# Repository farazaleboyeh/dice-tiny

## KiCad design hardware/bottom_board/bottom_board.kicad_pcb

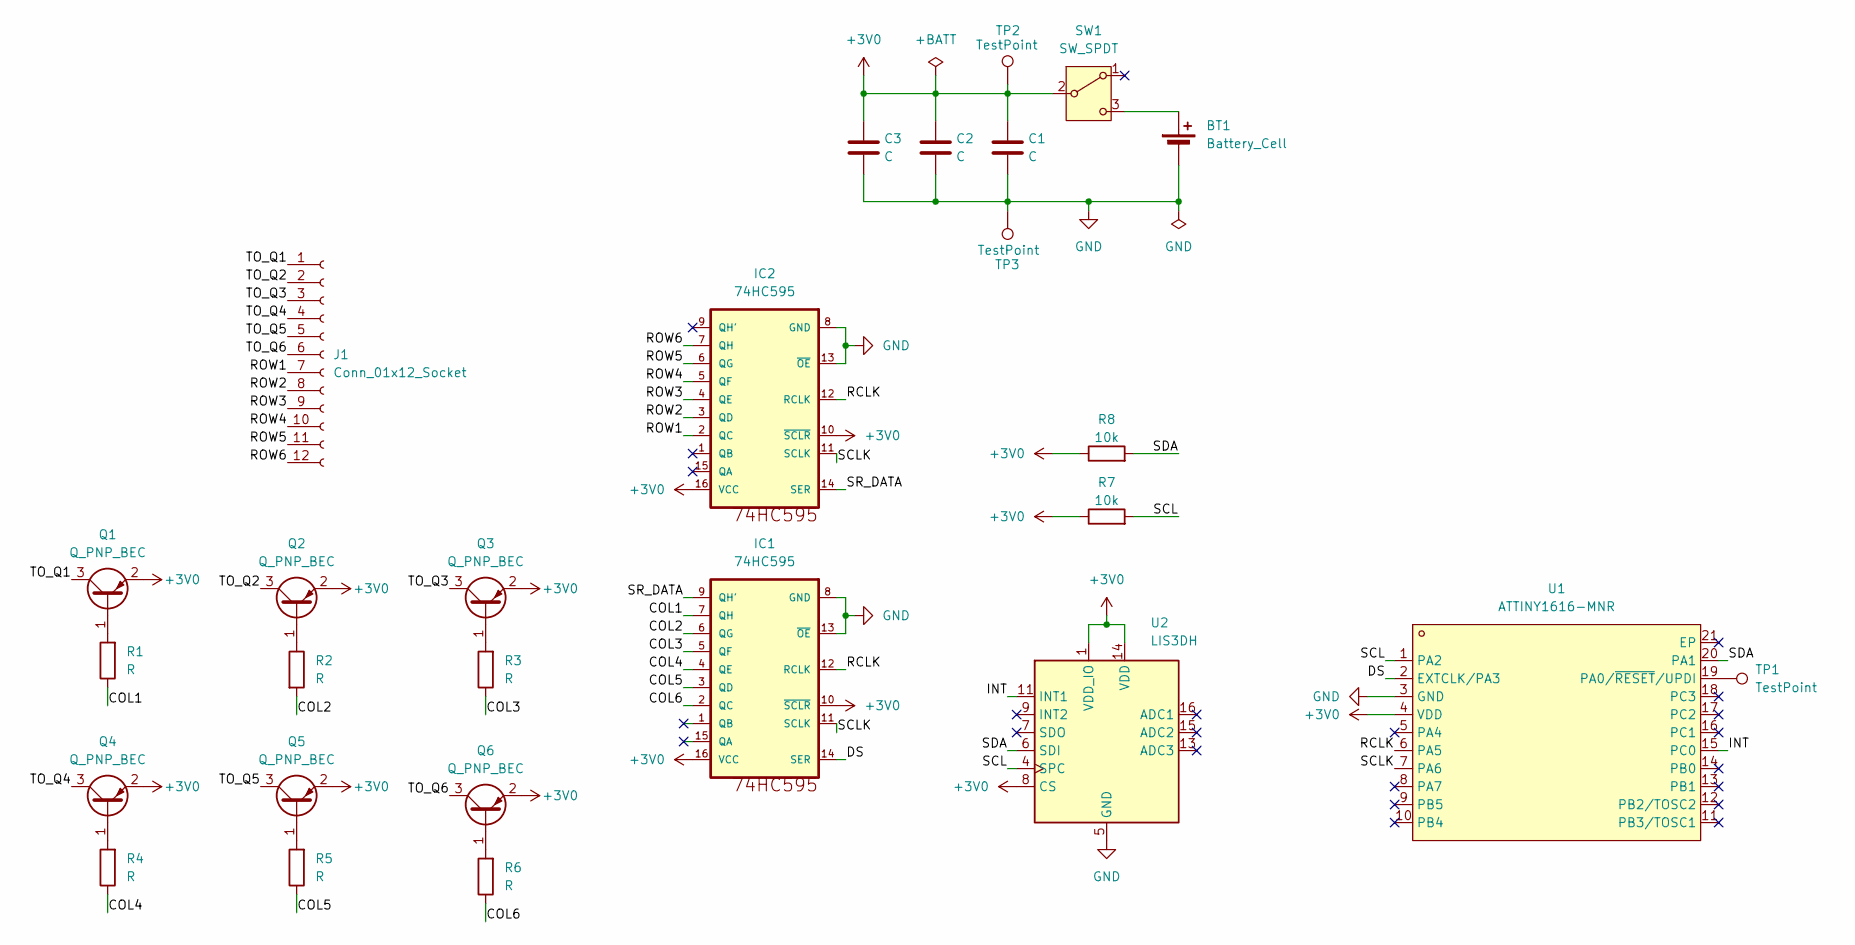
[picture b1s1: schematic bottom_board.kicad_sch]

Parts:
BT1: Battery_Cell; BAT-SMD_MY-2032-12-Updated-4; LCSC Part C6937139
C1, C3: C; C_0402_1005Metric
C2: C; C_0805_2012Metric
IC1, IC2: 74HC595; DHVQFN-16-1EP_2.5x3.5mm_P0.5mm_EP1x2mm
J1: Conn_01x12_Socket; PinSocket_1x12_P1.27mm_Vertical
Q1, Q2, Q3, Q4, Q5, Q6: Q_PNP_BEC; SOT-523
R1, R2, R3, R4, R5, R6: R; R_0402_1005Metric
R7, R8: 10k; R_0402_1005Metric
SW1: SW_SPDT; SW-SMD_MSK12CO2; LCSC Part C2681570
TP1, TP2, TP3: TestPoint; TestPoint_Pad_D1.0mm
U1: ATTINY1616-MNR; QFN-20_L3.0-W3.0-P0.40-BL-EP1.7; MPN ATTINY1616-MNR; LCSC Part C507118
U2: LIS3DH; LGA-16_3x3mm_P0.5mm_LayoutBorder3x5y

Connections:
+3V0: C1.1, C2.1, C3.1, IC1.10 (~SCLR), IC1.16 (VCC), IC2.10 (~SCLR), IC2.16 (VCC), Q1.2 (E), Q2.2 (E), Q3.2 (E), Q4.2 (E), Q5.2 (E), Q6.2 (E), R7.1, R8.1, SW1.2 (B), TP2.1 (1_1), U1.4 (VDD), U2.1 (VDD_IO), U2.8 (CS), U2.14 (VDD)
/COL1: IC1.7 (QH), R1.1
/COL2: IC1.6 (QG), R2.2
/COL3: IC1.5 (QF), R3.1
/COL4: IC1.4 (QE), R4.1
/COL5: IC1.3 (QD), R5.1
/COL6: IC1.2 (QC), R6.1
/DS: IC1.14 (SER), U1.2 (EXTCLK/PA3)
/INT: U1.15 (PC0), U2.11 (INT1)
/RCLK: IC1.12 (RCLK), IC2.12 (RCLK), U1.6 (PA5)
/ROW1: IC2.2 (QC), J1.7
/ROW2: IC2.3 (QD), J1.8
/ROW3: IC2.4 (QE), J1.9
/ROW4: IC2.5 (QF), J1.10
/ROW5: IC2.6 (QG), J1.11
/ROW6: IC2.7 (QH), J1.12
/SCL: R7.2, U1.1 (PA2), U2.4 (SPC)
/SCLK: IC1.11 (SCLK), IC2.11 (SCLK), U1.7 (PA6)
/SDA: R8.2, U1.20 (PA1), U2.6 (SDI)
/SR_DATA: IC1.9 (QH'), IC2.14 (SER)
/TO_Q1: J1.1, Q1.3 (C)
/TO_Q2: J1.2, Q2.3 (C)
/TO_Q3: J1.3, Q3.3 (C)
/TO_Q4: J1.4, Q4.3 (C)
/TO_Q5: J1.5, Q5.3 (C)
/TO_Q6: J1.6, Q6.3 (C)
GND: BT1.2 (-), C1.2, C2.2, C3.2, IC1.8 (GND), IC1.13 (~OE), IC2.8 (GND), IC2.13 (~OE), TP3.1 (1_1), U1.3 (GND), U2.5 (GND), U2.10 (GND), U2.12 (GND)
unnamed: BT1.1 (+), SW1.3 (C)
unnamed: Q1.1 (B), R1.2
unnamed: Q2.1 (B), R2.1
unnamed: Q3.1 (B), R3.2
unnamed: Q4.1 (B), R4.2
unnamed: Q5.1 (B), R5.2
unnamed: Q6.1 (B), R6.2
unnamed: TP1.1 (1_1), U1.19 (PA0/~RESET/UPDI)

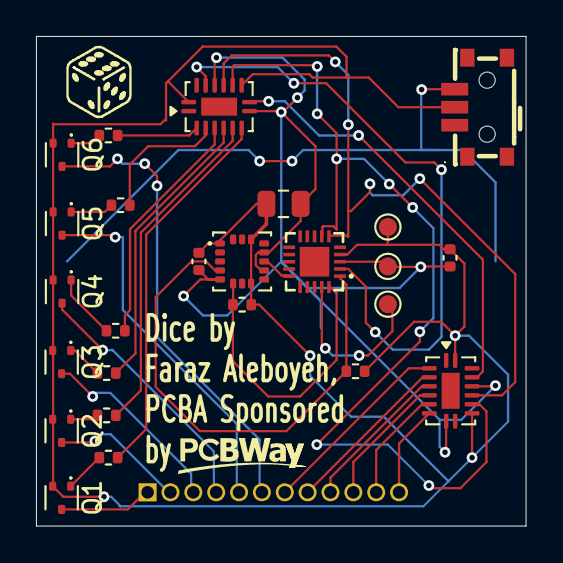
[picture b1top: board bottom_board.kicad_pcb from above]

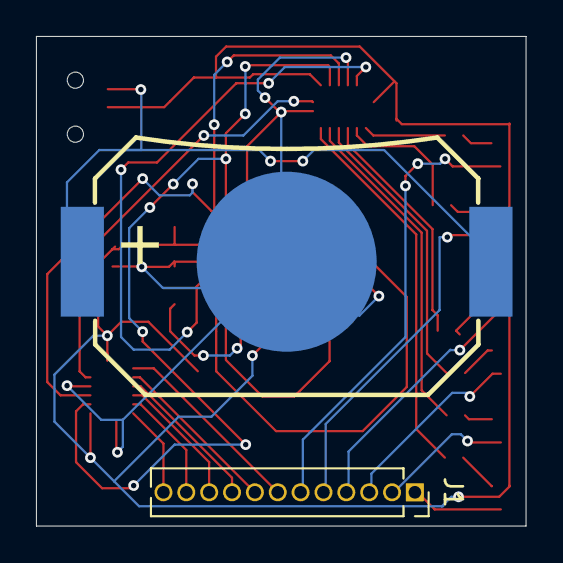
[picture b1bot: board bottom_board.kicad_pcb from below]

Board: 2 copper layers, 27.2 x 27.2 mm, 27 parts (2 on the bottom side), 35 nets.

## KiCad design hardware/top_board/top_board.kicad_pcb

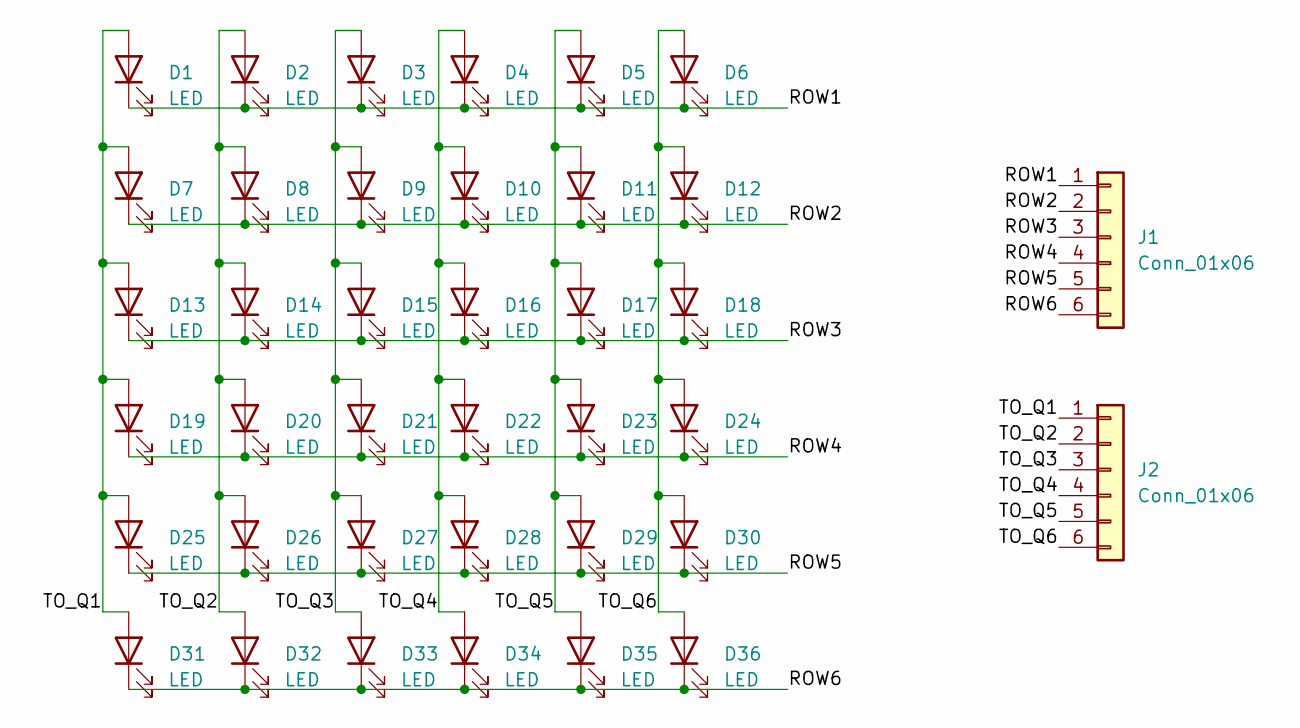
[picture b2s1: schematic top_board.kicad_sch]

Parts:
D1, D2, D3, D4, D5, D6, D7, D8, D9, D10, D11, D12, D13, D14, D15, D16, D17, D18, D19, D20, D21, D22, D23, D24, D25, D26, D27, D28, D29, D30, D31, D32, D33, D34, D35, D36: LED; LED_0603_1608Metric
J1, J2: Conn_01x06; PinHeader_1x06_P1.27mm_Vertical

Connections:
/ROW1: D1.1 (K), D2.1 (K), D3.1 (K), D4.1 (K), D5.1 (K), D6.1 (K), J1.1
/ROW2: D7.1 (K), D8.1 (K), D9.1 (K), D10.1 (K), D11.1 (K), D12.1 (K), J1.2
/ROW3: D13.1 (K), D14.1 (K), D15.1 (K), D16.1 (K), D17.1 (K), D18.1 (K), J1.3
/ROW4: D19.1 (K), D20.1 (K), D21.1 (K), D22.1 (K), D23.1 (K), D24.1 (K), J1.4
/ROW5: D25.1 (K), D26.1 (K), D27.1 (K), D28.1 (K), D29.1 (K), D30.1 (K), J1.5
/ROW6: D31.1 (K), D32.1 (K), D33.1 (K), D34.1 (K), D35.1 (K), D36.1 (K), J1.6
/TO_Q1: D1.2 (A), D7.2 (A), D13.2 (A), D19.2 (A), D25.2 (A), D31.2 (A), J2.1
/TO_Q2: D2.2 (A), D8.2 (A), D14.2 (A), D20.2 (A), D26.2 (A), D32.2 (A), J2.2
/TO_Q3: D3.2 (A), D9.2 (A), D15.2 (A), D21.2 (A), D27.2 (A), D33.2 (A), J2.3
/TO_Q4: D4.2 (A), D10.2 (A), D16.2 (A), D22.2 (A), D28.2 (A), D34.2 (A), J2.4
/TO_Q5: D5.2 (A), D11.2 (A), D17.2 (A), D23.2 (A), D29.2 (A), D35.2 (A), J2.5
/TO_Q6: D6.2 (A), D12.2 (A), D18.2 (A), D24.2 (A), D30.2 (A), D36.2 (A), J2.6

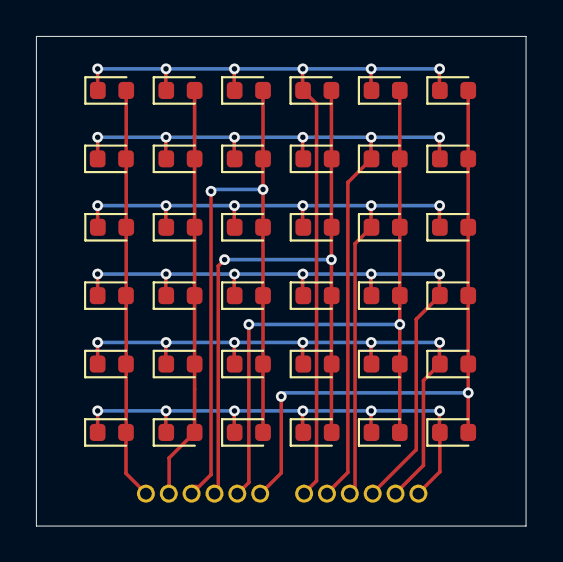
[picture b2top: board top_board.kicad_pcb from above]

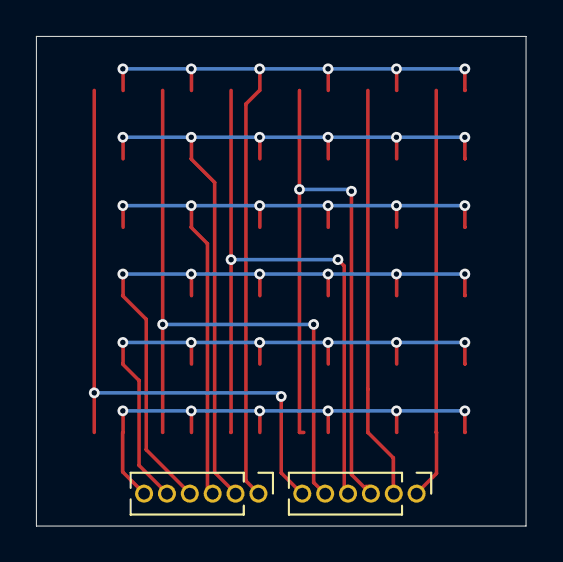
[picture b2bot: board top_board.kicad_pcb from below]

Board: 2 copper layers, 27.2 x 27.2 mm, 38 parts (2 on the bottom side), 12 nets.
